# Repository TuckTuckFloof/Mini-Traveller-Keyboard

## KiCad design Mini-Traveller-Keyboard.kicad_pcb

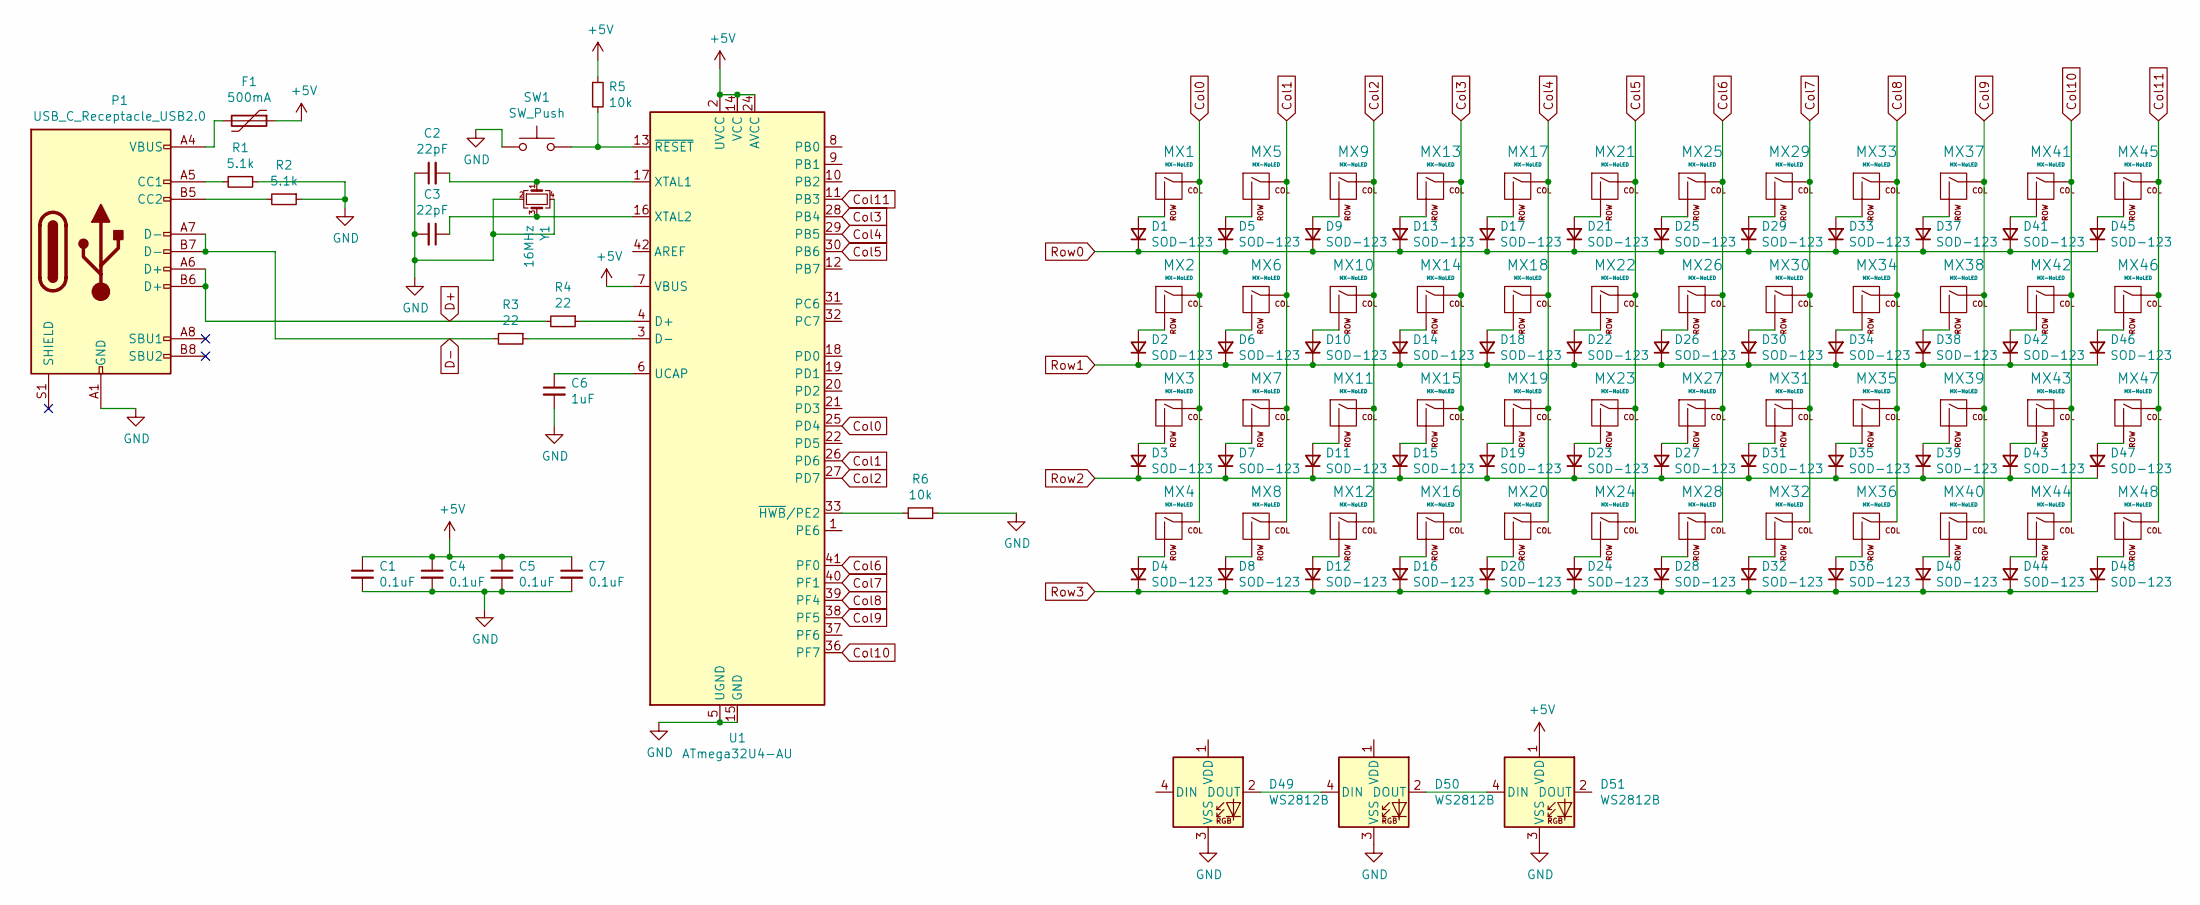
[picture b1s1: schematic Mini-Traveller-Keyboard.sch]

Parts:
C1, C4, C5, C7: 0.1uF; C_0805_2012Metric
C2, C3: 22pF; C_0805_2012Metric
C6: 1uF; C_0805_2012Metric
D1, D2, D3, D4, D5, D6, D7, D8, D9, D10, D11, D12, D13, D14, D15, D16, D17, D18, D19, D20, D21, D22, D23, D24, D25, D26, D27, D28, D29, D30, D31, D32, D33, D34, D35, D36, D37, D38, D39, D40, D41, D42, D43, D44, D45, D46, D47, D48: SOD-123; D_SOD-123
D49, D50, D51: WS2812B; LED_WS2812B_PLCC4_5.0x5.0mm_P3.2mm
F1: 500mA; Fuse_1206_3216Metric
MX1, MX2, MX3, MX4, MX5, MX6, MX7, MX8, MX9, MX10, MX11, MX12, MX13, MX14, MX15, MX16, MX17, MX18, MX19, MX20, MX21, MX22, MX23, MX24, MX25, MX26, MX27, MX28, MX29, MX30, MX31, MX32, MX33, MX34, MX35, MX36, MX37, MX38, MX39, MX40, MX41, MX42, MX43, MX44: MX-NoLED; MXOnly-1U-NoLED
MX45, MX46, MX47, MX48: MX-NoLED; MXOnly-1.75U-NoLED
P1: USB_C_Receptacle_USB2.0; USB_C_Receptacle_Amphenol_12401548E4-2A
R1, R2: 5.1k; R_0805_2012Metric
R3, R4: 22; R_0805_2012Metric
R5, R6: 10k; R_0805_2012Metric
SW1: SW_Push; SKQG-1155865
U1: ATmega32U4-AU; TQFP-44_10x10mm_P0.8mm
Y1: 16MHz; Crystal_SMD_3225-4Pin_3.2x2.5mm

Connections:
+5V: C1.1, C4.1, C5.1, C7.1, D51.1 (VDD), F1.1, R5.1, U1.2 (UVCC), U1.7 (VBUS), U1.14 (VCC), U1.24 (AVCC), U1.34 (VCC), U1.44 (AVCC)
Col0: MX1.1 (COL), MX2.1 (COL), MX3.1 (COL), MX4.1 (COL), U1.25 (PD4); also elsewhere on the board
Col1: MX5.1 (COL), MX6.1 (COL), MX7.1 (COL), MX8.1 (COL), U1.26 (PD6)
Col2: MX9.1 (COL), MX10.1 (COL), MX11.1 (COL), MX12.1 (COL), U1.27 (PD7); also elsewhere on the board
Col3: MX13.1 (COL), MX14.1 (COL), MX15.1 (COL), MX16.1 (COL), U1.28 (PB4); also elsewhere on the board
Col4: MX17.1 (COL), MX18.1 (COL), MX19.1 (COL), MX20.1 (COL), U1.29 (PB5)
Col5: MX21.1 (COL), MX22.1 (COL), MX23.1 (COL), MX24.1 (COL), U1.30 (PB6); also elsewhere on the board
Col6: MX25.1 (COL), MX26.1 (COL), MX27.1 (COL), MX28.1 (COL), U1.41 (PF0); also elsewhere on the board
Col7: MX29.1 (COL), MX30.1 (COL), MX31.1 (COL), MX32.1 (COL), U1.40 (PF1); also elsewhere on the board
Col8: MX33.1 (COL), MX34.1 (COL), MX35.1 (COL), MX36.1 (COL), U1.39 (PF4); also elsewhere on the board
Col9: MX37.1 (COL), MX38.1 (COL), MX39.1 (COL), MX40.1 (COL), U1.38 (PF5)
Col10: MX41.1 (COL), MX42.1 (COL), MX43.1 (COL), MX44.1 (COL), U1.36 (PF7); also elsewhere on the board
Col11: MX45.1 (COL), MX46.1 (COL), MX47.1 (COL), MX48.1 (COL), U1.11 (PB3)
D+: P1.A6 (D+), P1.B6 (D+), R4.2
D-: P1.A7 (D-), P1.B7 (D-), R3.2
GND: C1.2, C2.1, C3.2, C4.2, C5.2, C6.2, C7.2, D49.3 (VSS), D50.3 (VSS), D51.3 (VSS), P1.A1 (GND), P1.A12 (GND), P1.B1 (GND), P1.B12 (GND), R1.1, R2.1, R6.1, SW1.1, U1.5 (UGND), U1.15 (GND), U1.23 (GND), U1.35 (GND), U1.43 (GND), Y1.2, Y1.4
unnamed: C2.2, U1.17 (XTAL1), Y1.1
unnamed: C3.1, U1.16 (XTAL2), Y1.3
unnamed: C6.1, U1.6 (UCAP)
unnamed: D1.2 (A), MX1.2 (ROW)
unnamed: D2.2 (A), MX2.2 (ROW)
unnamed: D3.2 (A), MX3.2 (ROW)
unnamed 22: D4.2 (A), MX4.2 (ROW); also elsewhere on the board
unnamed: D5.2 (A), MX5.2 (ROW)
unnamed: D6.2 (A), MX6.2 (ROW)
unnamed: D7.2 (A), MX7.2 (ROW)
unnamed: D8.2 (A), MX8.2 (ROW)
unnamed: D9.2 (A), MX9.2 (ROW)
unnamed: D10.2 (A), MX10.2 (ROW)
unnamed: D11.2 (A), MX11.2 (ROW)
unnamed 30: D12.2 (A), MX12.2 (ROW); also elsewhere on the board
unnamed: D13.2 (A), MX13.2 (ROW)
unnamed: D14.2 (A), MX14.2 (ROW)
unnamed: D15.2 (A), MX15.2 (ROW)
unnamed 34: D16.2 (A), MX16.2 (ROW); also elsewhere on the board
unnamed: D17.2 (A), MX17.2 (ROW)
unnamed: D18.2 (A), MX18.2 (ROW)
unnamed: D19.2 (A), MX19.2 (ROW)
unnamed: D20.2 (A), MX20.2 (ROW)
unnamed: D21.2 (A), MX21.2 (ROW)
unnamed: D22.2 (A), MX22.2 (ROW)
unnamed: D23.2 (A), MX23.2 (ROW)
unnamed 42: D24.2 (A), MX24.2 (ROW); also elsewhere on the board
unnamed: D25.2 (A), MX25.2 (ROW)
unnamed: D26.2 (A), MX26.2 (ROW)
unnamed: D27.2 (A), MX27.2 (ROW)
unnamed 46: D28.2 (A), MX28.2 (ROW); also elsewhere on the board
unnamed: D29.2 (A), MX29.2 (ROW)
unnamed: D30.2 (A), MX30.2 (ROW)
unnamed: D31.2 (A), MX31.2 (ROW)
unnamed 50: D32.2 (A), MX32.2 (ROW); also elsewhere on the board
unnamed: D33.2 (A), MX33.2 (ROW)
unnamed: D34.2 (A), MX34.2 (ROW)
unnamed: D35.2 (A), MX35.2 (ROW)
unnamed 54: D36.2 (A), MX36.2 (ROW); also elsewhere on the board
unnamed: D37.2 (A), MX37.2 (ROW)
unnamed: D38.2 (A), MX38.2 (ROW)
unnamed: D39.2 (A), MX39.2 (ROW)
unnamed: D40.2 (A), MX40.2 (ROW)
unnamed: D41.2 (A), MX41.2 (ROW)
unnamed: D42.2 (A), MX42.2 (ROW)
unnamed: D43.2 (A), MX43.2 (ROW)
unnamed 62: D44.2 (A), MX44.2 (ROW); also elsewhere on the board
unnamed: D45.2 (A), MX45.2 (ROW)
unnamed: D46.2 (A), MX46.2 (ROW)
unnamed: D47.2 (A), MX47.2 (ROW)
unnamed: D48.2 (A), MX48.2 (ROW)
unnamed: D49.2 (DOUT), D50.4 (DIN)
unnamed: D50.2 (DOUT), D51.4 (DIN)
unnamed: F1.2, P1.A4 (VBUS), P1.A9 (VBUS), P1.B4 (VBUS), P1.B9 (VBUS)
unnamed: P1.A5 (CC1), R1.2
unnamed: P1.B5 (CC2), R2.2
unnamed: R3.1, U1.3 (D-)
unnamed: R4.1, U1.4 (D+)
unnamed: R5.2, SW1.2, U1.13 (~RESET)
unnamed: R6.2, U1.33 (~HWB~/PE2)
Row0: D1.1 (K), D5.1 (K), D9.1 (K), D13.1 (K), D17.1 (K), D21.1 (K), D25.1 (K), D29.1 (K), D33.1 (K), D37.1 (K), D41.1 (K), D45.1 (K)
Row1: D2.1 (K), D6.1 (K), D10.1 (K), D14.1 (K), D18.1 (K), D22.1 (K), D26.1 (K), D30.1 (K), D34.1 (K), D38.1 (K), D42.1 (K), D46.1 (K)
Row2: D3.1 (K), D7.1 (K), D11.1 (K), D15.1 (K), D19.1 (K), D23.1 (K), D27.1 (K), D31.1 (K), D35.1 (K), D39.1 (K), D43.1 (K), D47.1 (K)
Row3: D4.1 (K), D8.1 (K), D12.1 (K), D16.1 (K), D20.1 (K), D24.1 (K), D28.1 (K), D32.1 (K), D36.1 (K), D40.1 (K), D44.1 (K), D48.1 (K)

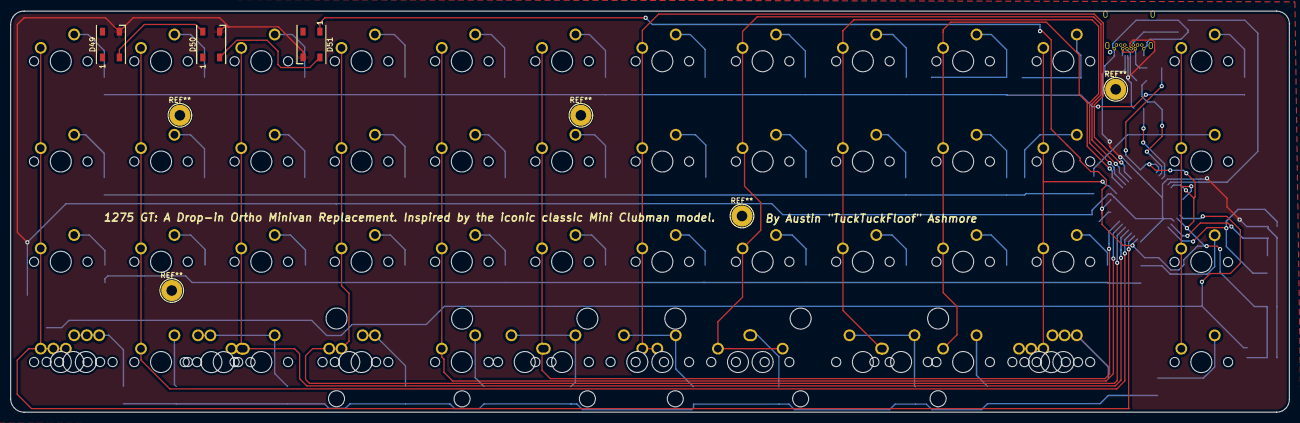
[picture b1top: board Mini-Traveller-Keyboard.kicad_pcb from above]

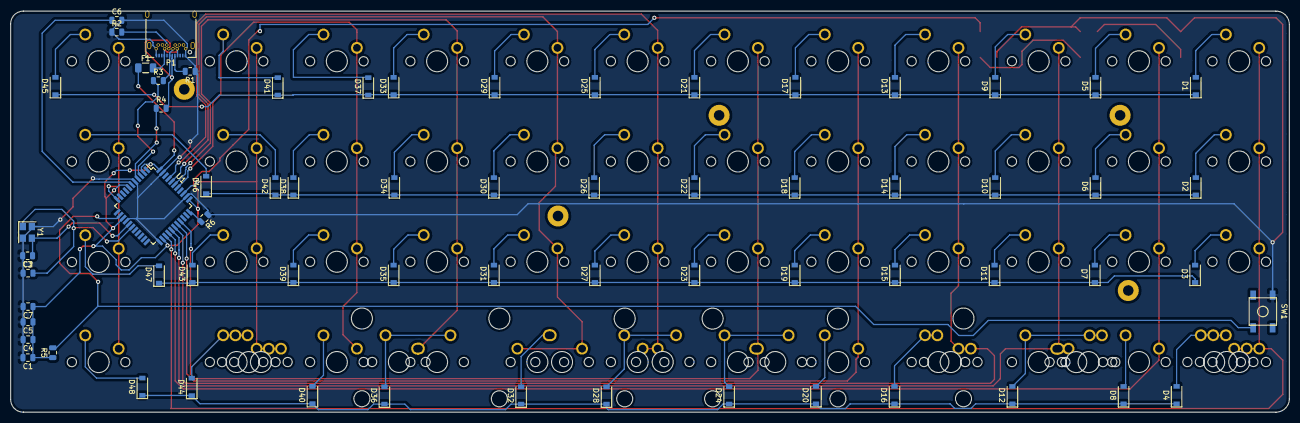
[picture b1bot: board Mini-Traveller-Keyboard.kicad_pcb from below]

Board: 2 copper layers, 243.0 x 76.2 mm, 128 parts (72 on the bottom side), 80 nets.

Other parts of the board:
MX4#2, MX4#3, MX12#2, MX12#3, MX16#2, MX24#2, MX28#2, MX32#2, MX36#2, MX44#2, MX44#3: MX-NoLED; MXOnly-1U-NoLED

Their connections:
Col0: MX4#2.1, MX4#3.1; also elsewhere on the board
Col2: MX12#2.1, MX12#3.1; also elsewhere on the board
Col3: MX16#2.1; also elsewhere on the board
Col5: MX24#2.1; also elsewhere on the board
Col6: MX28#2.1; also elsewhere on the board
Col7: MX32#2.1; also elsewhere on the board
Col8: MX36#2.1; also elsewhere on the board
Col10: MX44#2.1, MX44#3.1; also elsewhere on the board
unnamed 22: MX4#2.2, MX4#3.2; also elsewhere on the board
unnamed 30: MX12#2.2, MX12#3.2; also elsewhere on the board
unnamed 34: MX16#2.2; also elsewhere on the board
unnamed 42: MX24#2.2; also elsewhere on the board
unnamed 46: MX28#2.2; also elsewhere on the board
unnamed 50: MX32#2.2; also elsewhere on the board
unnamed 54: MX36#2.2; also elsewhere on the board
unnamed 62: MX44#2.2, MX44#3.2; also elsewhere on the board

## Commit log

2020-09-29 Initial Commit + Submodules added for the MTK
2020-09-30 Completed the outline of the pcb, just need to route and trace now
2020-10-01 Finished the basic layout and have all the bottom rows ready to go
2020-10-13 Finished the main layout, cutouts need to be done
2020-10-14 Main wiring has commenced
2020-10-21 Finished main PCB design, waiting on silk
2021-06-16 files
